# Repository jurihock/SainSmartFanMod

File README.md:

# SainSmart solder fume extractor modification

This project is about replacing the default AC fan in the [SainSmart solder fume extractor](https://www.sainsmart.com/products/sainsmart-solder-smoke-absorber-remover-fume-extractor-for-soldering) with a DC fan like [Noctua NF-A14](https://www.noctua.at/en/products/nf-a14-industrialppc-3000-pwm).

## Why?

- the built-in fan is way too loud
- it runs at constant speed only
- the power cable is way too stiff

## Features

- toggle switch to power the device on or off integrated in the housing
- dual LED to indicate power on and standby
- MOSFET switch to turn the fan on or off using MCU
- pot with a large knob 🫠 to select the fan speed

## Thoughts

### Electrical

In fact, the Noctua fan draws around 2A during the initial turn. I decided to use a logic-level MOSFET to switch the fan on. Adding a cap between 10uF and 100uF increases the Miller effect, forcing the fan to start up slowly and reducing the initial current as well. But in this case, an NPN transistor is needed to ground the PWM signal against the N-MOSFET drain.

I'm unsure whether a DC fan requires a flyback diode. I decided to skip it for now.

### Mechanical

The JST connectors are intentionally placed on the edges, which puts mechanical stress on the board. There is certainly a better solution for connector placement.

## How it looks like

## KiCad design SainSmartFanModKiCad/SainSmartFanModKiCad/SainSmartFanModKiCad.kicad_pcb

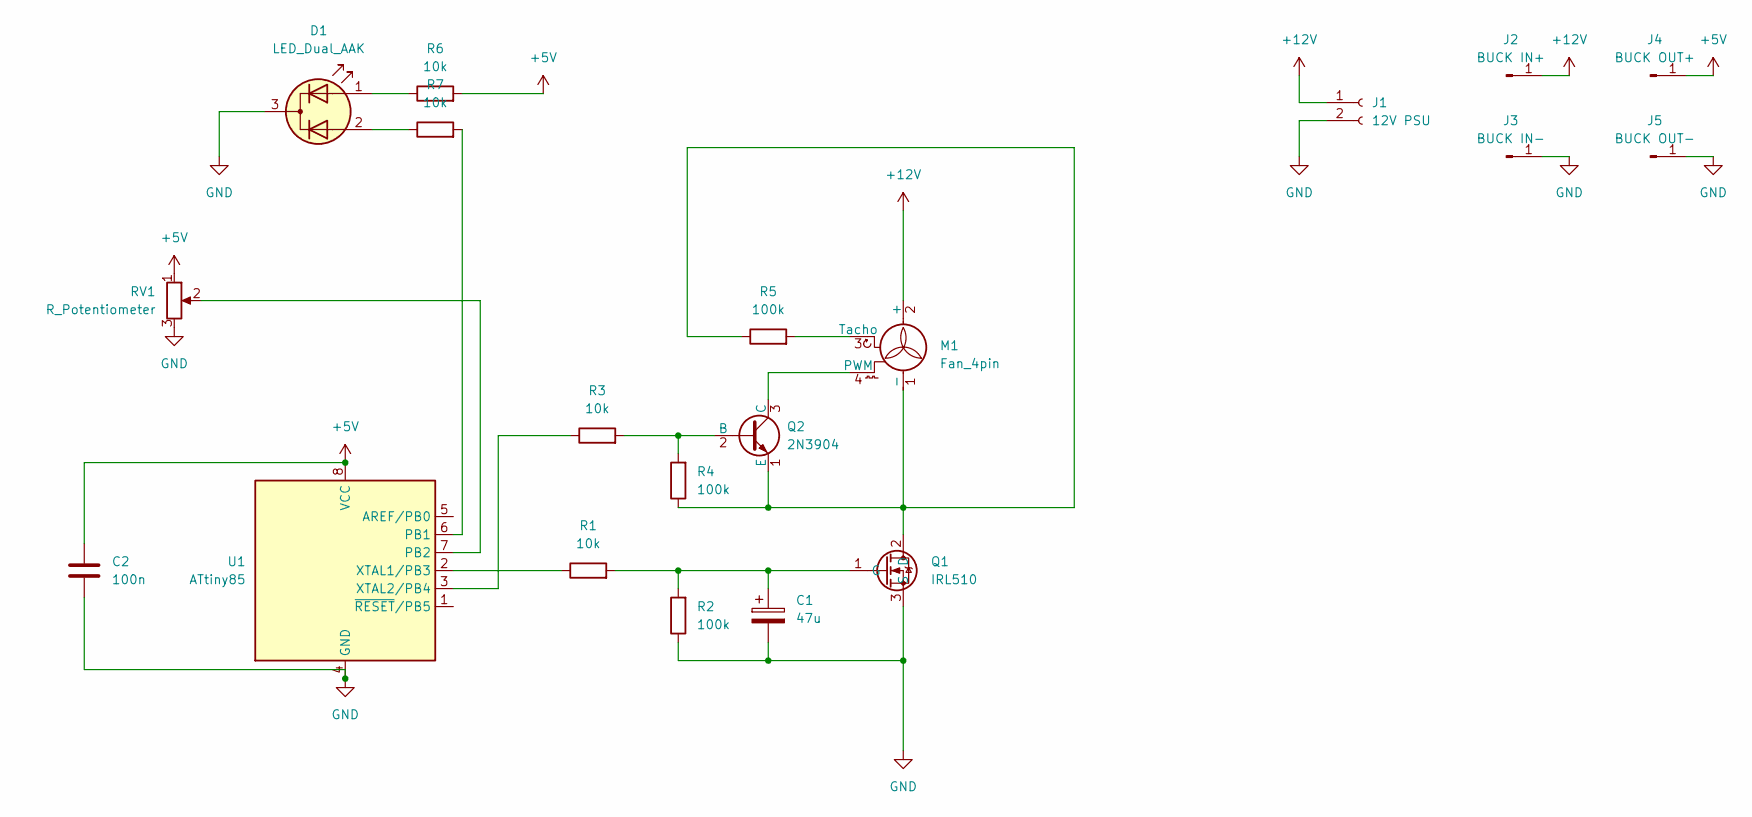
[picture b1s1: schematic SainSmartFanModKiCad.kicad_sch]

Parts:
C1: 47u; CP_Radial_D6.3mm_P2.50mm
C2: 100n; C_Disc_D3.0mm_W2.0mm_P2.50mm
D1: LED_Dual_AAK; JST_EH_B3B-EH-A_1x03_P2.50mm_Vertical
J1: 12V PSU; JST_EH_B2B-EH-A_1x02_P2.50mm_Vertical
J2: BUCK IN+; PinHeader_1x01_P1.00mm_Vertical
J3: BUCK IN-; PinHeader_1x01_P1.00mm_Vertical
J4: BUCK OUT+; PinHeader_1x01_P1.00mm_Vertical
J5: BUCK OUT-; PinHeader_1x01_P1.00mm_Vertical
M1: Fan_4pin; JST_EH_B4B-EH-A_1x04_P2.50mm_Vertical
Q1: IRL510; TO-220-3_Vertical
Q2: 2N3904; TO-92_Inline_Wide
R1, R3, R6, R7: 10k; R_Axial_DIN0207_L6.3mm_D2.5mm_P10.16mm_Horizontal
R2, R4, R5: 100k; R_Axial_DIN0207_L6.3mm_D2.5mm_P10.16mm_Horizontal
RV1: R_Potentiometer; JST_EH_B3B-EH-A_1x03_P2.50mm_Vertical
U1: ATtiny85; DIP-8_W7.62mm

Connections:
+5V: C2.1, J4.1, R6.2, RV1.1, U1.8 (VCC)
+12V: J1.1, J2.1, M1.2 (+)
GND: C1.2, C2.2, D1.3 (K), J1.2, J3.1, J5.1, Q1.3 (S), R2.1, RV1.3, U1.4 (GND)
unnamed: D1.1 (A1), R6.1
unnamed: D1.2 (A2), R7.1
unnamed: M1.1 (-), Q1.2 (D), Q2.1 (E), R4.1, R5.1
unnamed: M1.4 (PWM), Q2.3 (C)
unnamed: M1.3 (Tacho), R5.2
unnamed: C1.1, Q1.1 (G), R1.2, R2.2
unnamed: Q2.2 (B), R3.2, R4.2
unnamed: R7.2, U1.6 (PB1)
unnamed: RV1.2, U1.7 (PB2)
unnamed: R1.1, U1.2 (XTAL1/PB3)
unnamed: R3.1, U1.3 (XTAL2/PB4)

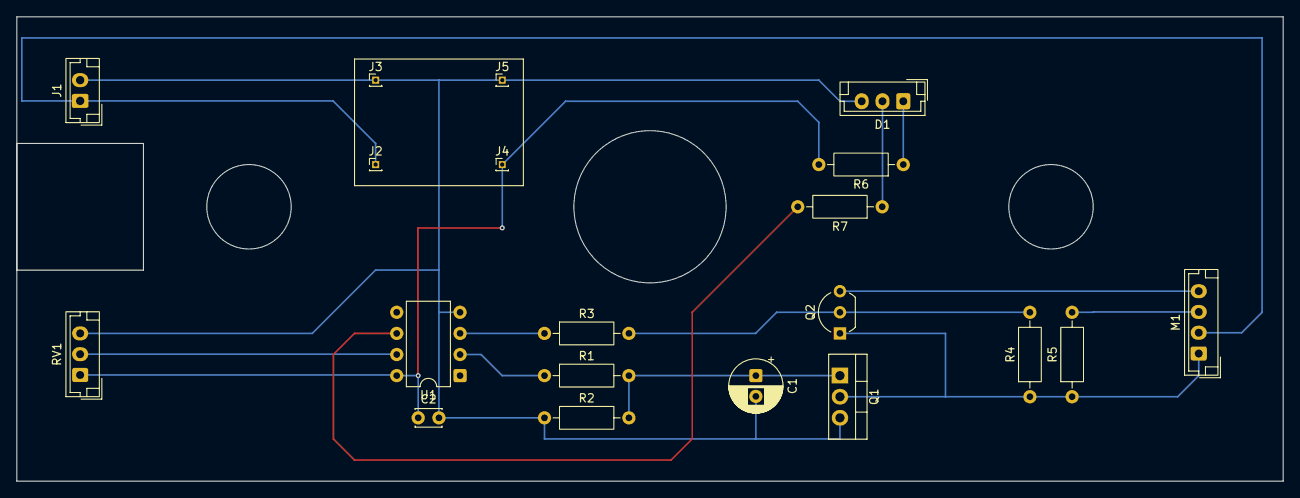
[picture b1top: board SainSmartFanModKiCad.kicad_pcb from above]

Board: 2 copper layers, 152.4 x 55.9 mm, 20 parts (0 on the bottom side), 14 nets.

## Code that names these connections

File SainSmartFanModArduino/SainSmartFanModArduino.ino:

// ATtiny85:  ArduinoISP + ATTinyCore
// Clock:     8 MHz (internal)
// PWM:       25 kHz on PB4 (D4, OC1B) using Timer1 with PLL clock and /16 prescaler
// FAN:       PB3 (D3), MOSFET gate
// POT:       A1 (PB2)

const uint8_t FAN = 3;    // PB3 -> MOSFET gate (HIGH = ON)
const uint8_t PWM = 4;    // PB4 -> OC1B -> NPN base (sinks fan PWM, active-low at fan)
const uint8_t LED = 1;    // PB1
const uint8_t POT = A1;   // PB2
const uint8_t TOP = 159;  // Timer1 TOP for 25 kHz: f = (PLL 64MHz / 16) / (TOP+1) = 4MHz / 160 = 25kHz
const float   MIN = 0.2f; // min. duty cycle 20%

float getDuty()
{
  float duty = analogRead(POT) / 1023.0f;
  
  duty = powf(duty, 1.5f); // apply gamma
  duty = duty * (1.0f - MIN) + MIN; // scale to 20%..100%

  return duty;
}

void setDuty(float duty)
{
  duty = constrain(duty, 0.0f, 1.0f);
  duty = 1.0f - duty; // active-low at fan (NPN sink)

  uint16_t ticks = (uint16_t)((TOP + 1) * duty);

  if (ticks > 0)
  {
    ticks -= 1;
  }

  OCR1B = (uint8_t)ticks;
}

void setFan(bool state)
{
  if (state)
  {
    digitalWrite(LED, LOW);  // LED OFF
    pinMode(PWM, OUTPUT);
    GTCCR |= _BV(COM1B1);    // enable OC1B on pin (non-inverting)
    digitalWrite(FAN, HIGH); // MOSFET ON
    delay(1000);
  }
  else
  {
    digitalWrite(LED, HIGH); // LED ON
    digitalWrite(FAN, LOW);  // MOSFET OFF
    delay(1000);             // let it settle
    GTCCR &= ~_BV(COM1B1);   // disconnect OC1B from pin
    pinMode(PWM, INPUT);     // Hi-Z to avoid backfeed
  }
}

void setup()
{
  pinMode(FAN, OUTPUT);
  pinMode(PWM, OUTPUT);
  pinMode(LED, OUTPUT);

  // Enable PLL and route to Timer1
  PLLCSR = _BV(PLLE);                 // enable PLL
  delay(2);
  while (!(PLLCSR & _BV(PLOCK))) {}   // wait for lock
  PLLCSR |= _BV(PCKE);                // PLL clock to Timer1

  // Timer1 setup: Fast PWM, TOP = OCR1C, non-inverting on OC1B, prescaler = /16
  TCCR1 = 0;
  GTCCR = 0;

  // Prescaler /16 and PWM enable
  TCCR1 = _BV(PWM1A) | _BV(CS12) | _BV(CS10);  // CS1x = 0b0101 -> /16
  GTCCR = _BV(PWM1B) | _BV(COM1B1);            // enable OC1B, non-inverting

  OCR1C = TOP;     // sets 25 kHz
  OCR1B = 0;       // start at 0% (line high at fan)

  setFan(false);
}

void loop()
{
  static float oldDuty = MIN;
  static bool oldState = false;

  float newDuty = (getDuty() + oldDuty) / 2.0f;
  bool newState = oldState;

  // schmitt trigger around MIN
  float newDelta = newDuty - MIN;

  if (!newState && newDelta >= 0.03f)
  {
    // turn ON when duty ≥ MIN + 3%
    newState = true;
  }
  else if (newState && newDelta <= 0.01f)
  {
    // turn OFF when duty ≤ MIN + 1%
    newState = false;
  }

  if (newDuty != oldDuty)
  {
    setDuty(newDuty);
  }

  if (newState != oldState)
  {
    setFan(newState);
  }

  oldDuty = newDuty;
  oldState = newState;

  delay(100);
}

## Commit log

2026-04-05 Add sources
2026-04-05 Move files
2026-04-05 Enhance README with project details and features
    Expanded project description and added sections on reasons and features.
2026-04-05 Add user manual
2026-04-05 Add assets
2026-04-05 Convert images
2026-04-05 Rename
2026-04-05 Enhance README with usage images and instructions
    Added images and section on how to use the device.
2026-04-05 Remove obsolete files
2026-04-05 Compress images
2026-04-06 Improve clarity in electrical section of README
    Reworded sentences for clarity and conciseness in the README.
